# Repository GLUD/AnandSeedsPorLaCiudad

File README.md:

# AnandSeedsPorLaCiudad
# Anand Seeds
This project is about "soberanía alimentaria" for our communities and world.

Este proyecto de desarrollo colaborativo, esta basado en [Métodologías ágiles para el desarrollo de software: eXtreme Programming (XP)](http://www.cyta.com.ar/ta0502/v5n2a1.htm)

### Descripción del proyecto ###

[Marco Devpost](http://devpost.com/software/anand-seeds)

### Historial de versiones ###

1,1 Liberado en Mayo del 2015
1,2 Liberado en Agosto del 2015

### INFORMACIÓN DE CONTACTO ANAND SEEDS ###
Facebook: https://www.facebook.com/anandseeds   
Twitter: https://twitter.com/AnandSeeds   
E-mail: anandseeds21@gmail.com   

### INFORMACIÓN DE CONTACTO DESARROLLADORES ###

* Desarrollador: Ivan Camilo Ruiz Mongui  
Ingeniero Electrónico de la UDistrital FJC  
Movil: 3209025813  
Facebook: Ivan Camilo Ruiz  
Twitter: @camiloud Linkedin: Iván Camilo Ruiz  

* Desarrollador: Jorge Ulises Useche Cuellar  
Est.Ingeniería Electónica de la Udistrital FJC  
Movil: 3114813719  
Facebook: Jorge Ulises  
Twitter: @juusechec  

* Desarrollador: Diego Javier Mena Amado  
Est. Ingeniería Electrónica de la UDistrital FJC  
Movil: 3133067541 
Facebook: Diego Javier Brown 
Twitter: @ DiegoJavierMena

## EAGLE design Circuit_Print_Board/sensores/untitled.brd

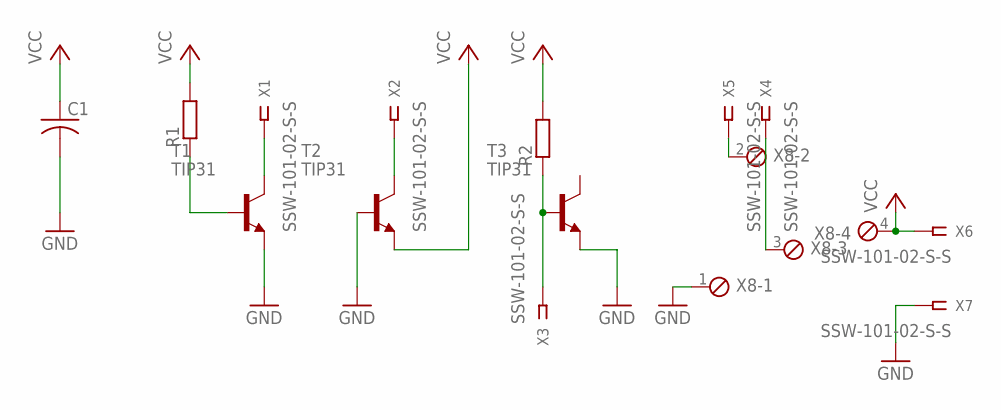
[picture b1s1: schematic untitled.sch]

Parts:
C1: C-US050-025X075; C050-025X075
R1, R2: R-EU_0204/7; 0204/7
T1, T2, T3: TIP31; TO220
X1, X2, X3, X4, X5, X6, X7: SSW-101-02-S-S
X8: MPT4; 4POL254

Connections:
GND: C1.2, T1.3 (E), T2.1 (B), T3.3 (E), X7.1, X8.1
unnamed: R1.1, T1.1 (B)
unnamed: T1.2 (C), X1.1
unnamed: T2.2 (C), X2.1
unnamed: R2.1, T3.1 (B), X3.1
unnamed: X5.1, X8.2
unnamed: X4.1, X8.3
VCC: C1.1, R1.2, R2.2, T2.3 (E), X6.1, X8.4

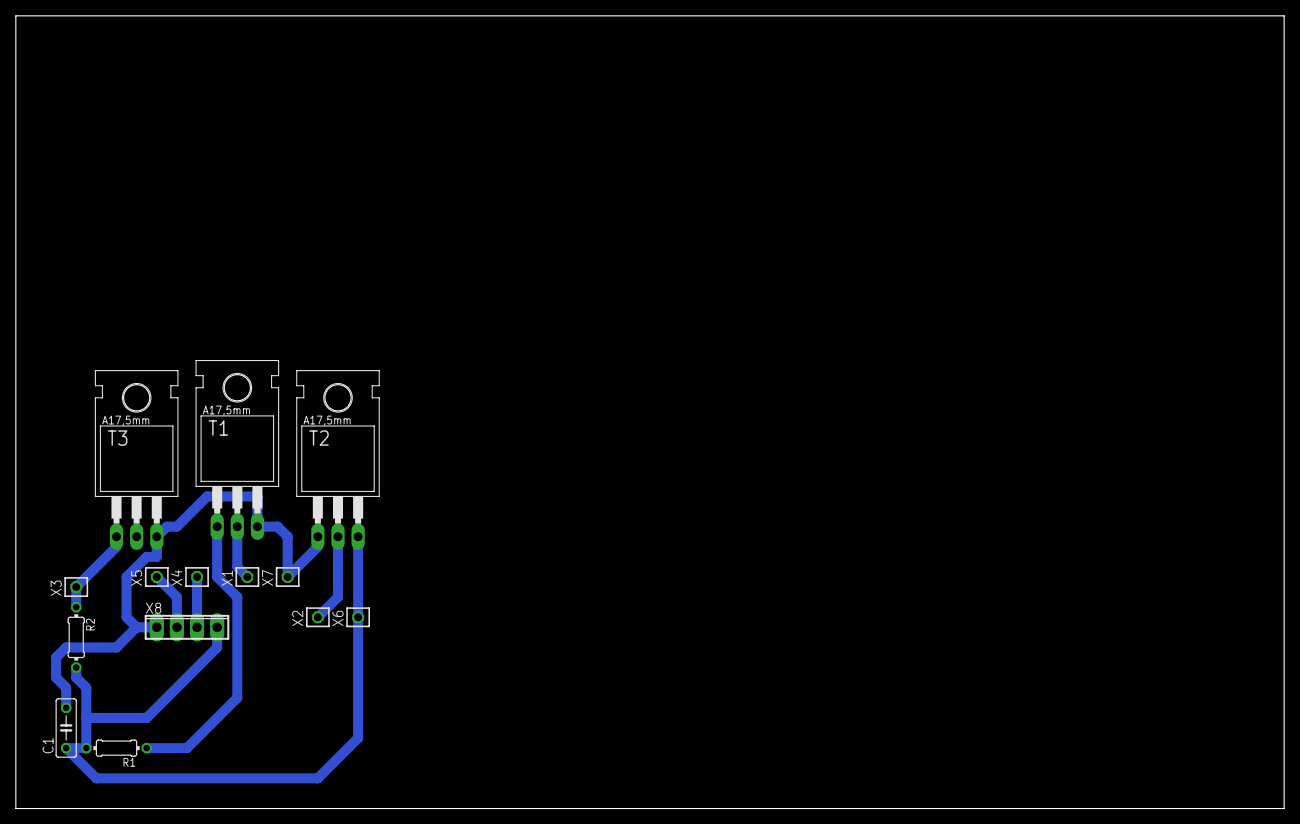
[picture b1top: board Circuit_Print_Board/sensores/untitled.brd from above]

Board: 2 copper layers, 160.0 x 100.0 mm, 14 parts (0 on the bottom side), 8 nets.

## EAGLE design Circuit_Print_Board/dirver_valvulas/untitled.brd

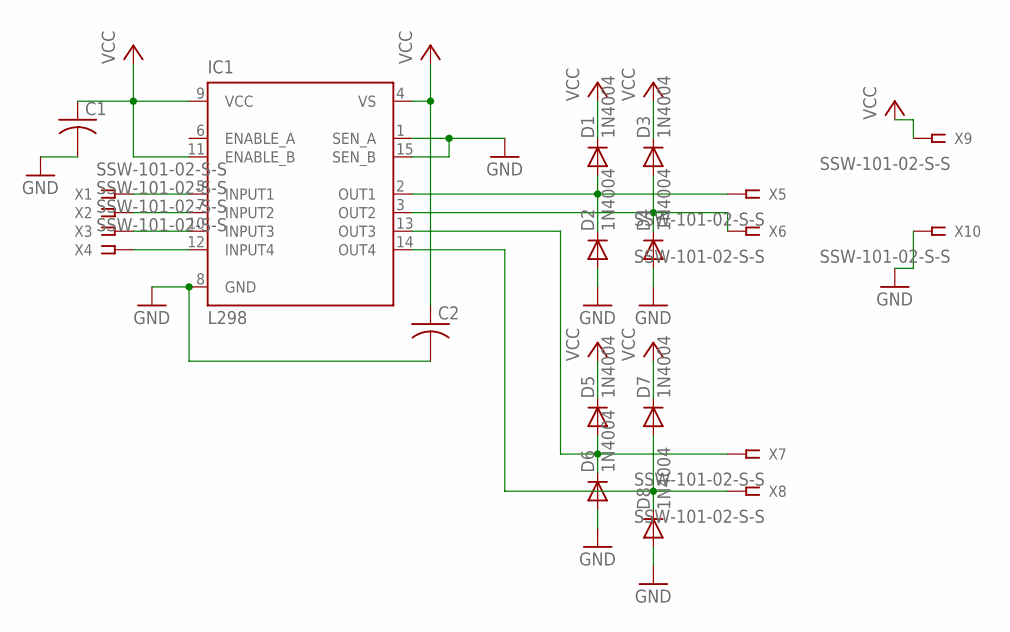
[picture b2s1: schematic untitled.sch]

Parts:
C1, C2: C-US025-025X050; C025-025X050
D1, D2, D3, D4, D5, D6, D7, D8: 1N4004; DO41-10
IC1: L298; MULTIWATT-15
X1, X2, X3, X4, X5, X6, X7, X8, X9, X10: SSW-101-02-S-S

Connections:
GND: C1.2, C2.2, D2.A, D4.A, D6.A, D8.A, IC1.1 (SEN_A), IC1.8 (GND), IC1.15 (SEN_B), X10.1
unnamed: IC1.5 (INPUT1), X1.1
unnamed: IC1.7 (INPUT2), X2.1
unnamed: IC1.10 (INPUT3), X3.1
unnamed: IC1.12 (INPUT4), X4.1
unnamed: D1.A, D2.C, IC1.2 (OUT1), X5.1
unnamed: D3.A, D4.C, IC1.3 (OUT2), X6.1
unnamed: D5.A, D6.C, IC1.13 (OUT3), X7.1
unnamed: D7.A, D8.C, IC1.14 (OUT4), X8.1
VCC: C1.1, C2.1, D1.C, D3.C, D5.C, D7.C, IC1.4 (VS), IC1.9 (VCC), IC1.11 (ENABLE_B), X9.1

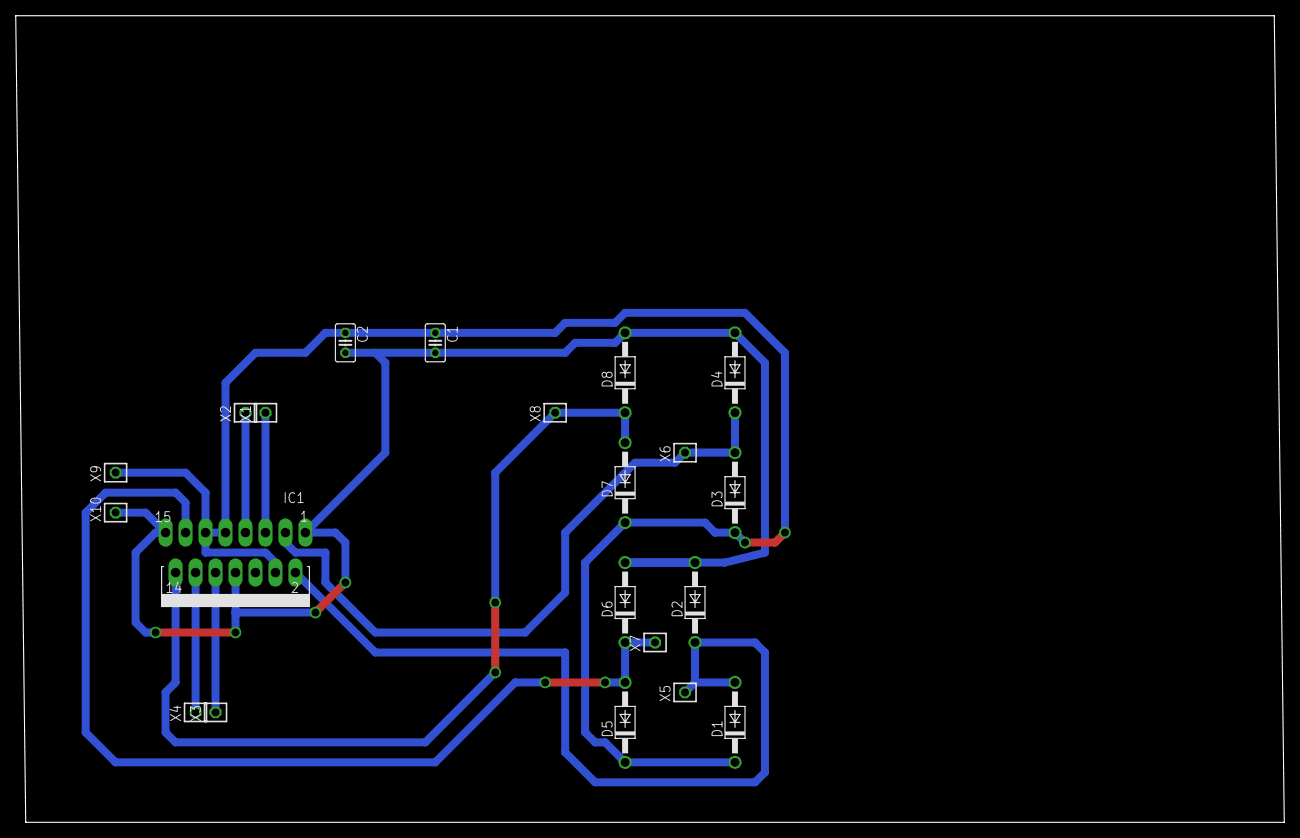
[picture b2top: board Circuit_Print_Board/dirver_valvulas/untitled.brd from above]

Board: 2 copper layers, 161.3 x 102.5 mm, 21 parts (0 on the bottom side), 10 nets.

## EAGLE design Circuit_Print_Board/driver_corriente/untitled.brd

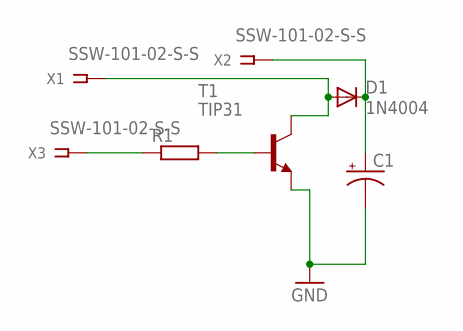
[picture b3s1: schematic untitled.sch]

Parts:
C1: CPOL-USE5-5; E5-5
D1: 1N4004; DO41-10
R1: R-EU_0207/10; 0207/10
T1: TIP31; TO220
X1, X2, X3: SSW-101-02-S-S

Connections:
GND: C1.-, T1.3 (E)
unnamed: R1.2, T1.1 (B)
unnamed: D1.A, T1.2 (C), X1.1
unnamed: C1.+, D1.C, X2.1
unnamed: R1.1, X3.1

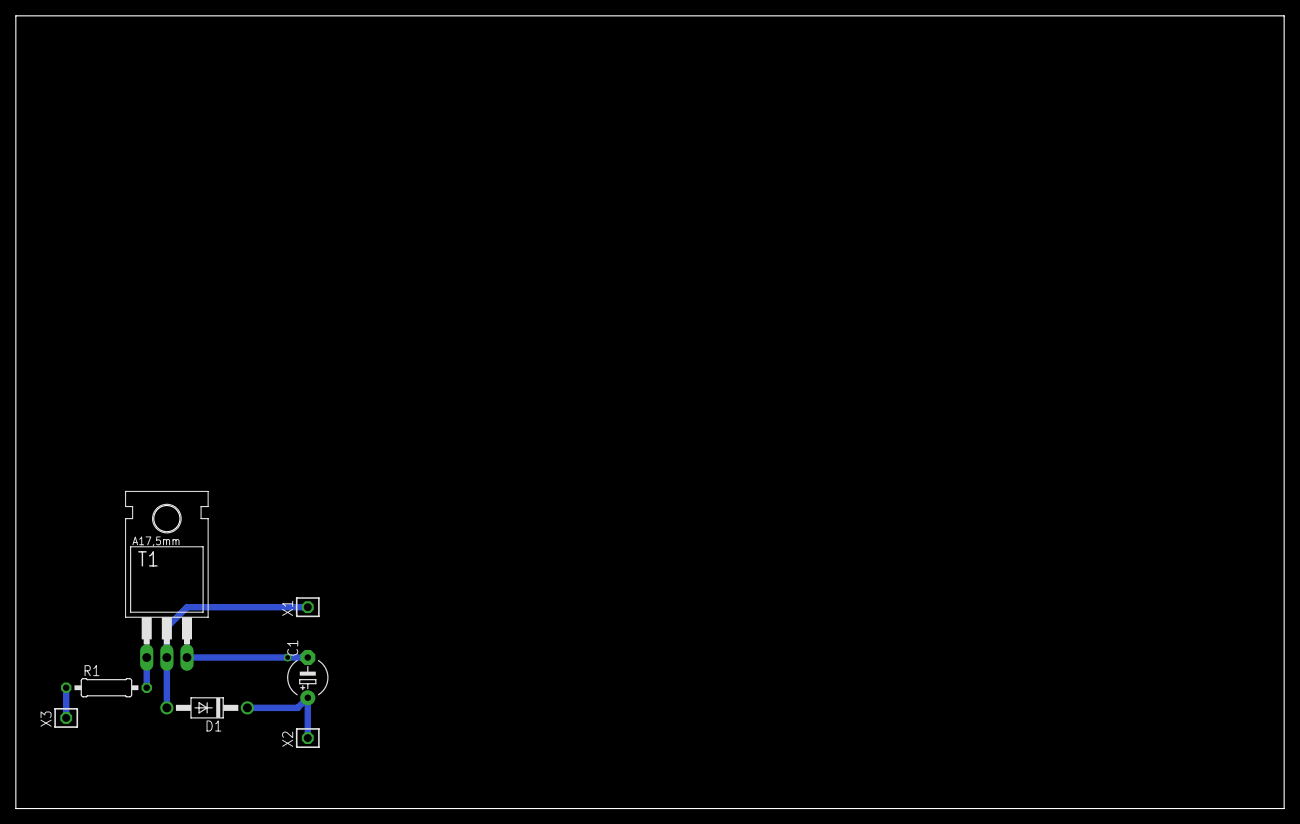
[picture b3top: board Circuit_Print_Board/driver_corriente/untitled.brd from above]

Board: 2 copper layers, 160.0 x 100.0 mm, 7 parts (0 on the bottom side), 5 nets.

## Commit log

2015-08-21 Agregando archivos de circuitos impresos
2015-08-21 Pagina inicial de configuración symfony4
2015-08-21 Script de comunicación serial entre raspberry y arduino
2015-08-21 Se añaden las salidas de los PCB
2015-08-21 Se añaden los datos de contacto y el enlace a Devpost
2015-08-21 Se añade algoritmo en python para acciones de Arduinos desde la web
